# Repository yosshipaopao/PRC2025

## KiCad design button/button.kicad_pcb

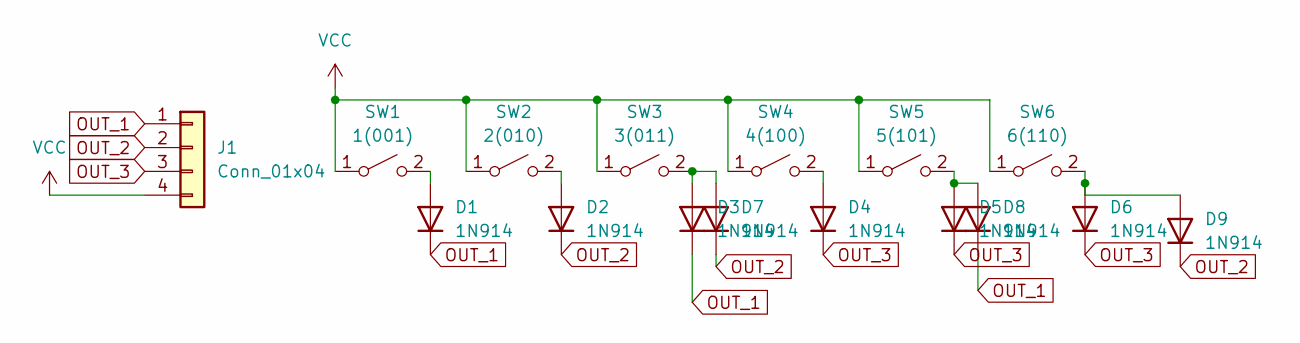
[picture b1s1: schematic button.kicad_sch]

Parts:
D1, D2, D3, D4, D5, D6, D7, D8, D9: 1N914; D_SOD-523
J1: Conn_01x04; PinSocket_1x04_P2.54mm_Vertical
SW1: 1(001); SW_PUSH_6mm
SW2: 2(010); SW_PUSH_6mm
SW3: 3(011); SW_PUSH_6mm
SW4: 4(100); SW_PUSH_6mm
SW5: 5(101); SW_PUSH_6mm
SW6: 6(110); SW_PUSH_6mm

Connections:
unnamed: D1.2 (A), SW1.2 (B)
unnamed: D2.2 (A), SW2.2 (B)
unnamed: D3.2 (A), D7.2 (A), SW3.2 (B)
unnamed: D4.2 (A), SW4.2 (B)
unnamed: D5.2 (A), D8.2 (A), SW5.2 (B)
unnamed: D6.2 (A), D9.2 (A), SW6.2 (B)
OUT_1: D1.1 (K), D3.1 (K), D8.1 (K), J1.1
OUT_2: D2.1 (K), D7.1 (K), D9.1 (K), J1.2
OUT_3: D4.1 (K), D5.1 (K), D6.1 (K), J1.3
VCC: J1.4, SW1.1 (A), SW2.1 (A), SW3.1 (A), SW4.1 (A), SW5.1 (A), SW6.1 (A)

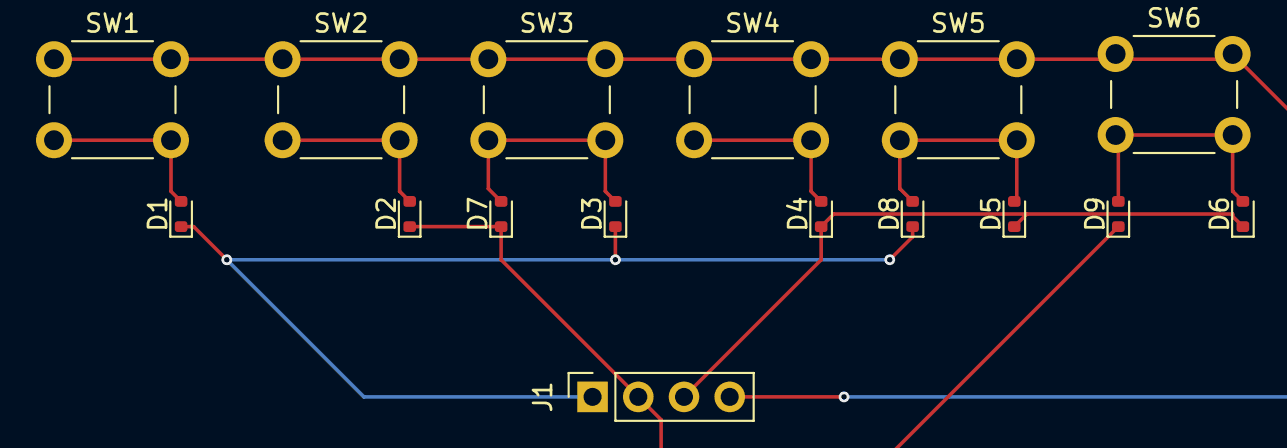
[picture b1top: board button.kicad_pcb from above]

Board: 2 copper layers, 16 parts (0 on the bottom side), 10 nets.

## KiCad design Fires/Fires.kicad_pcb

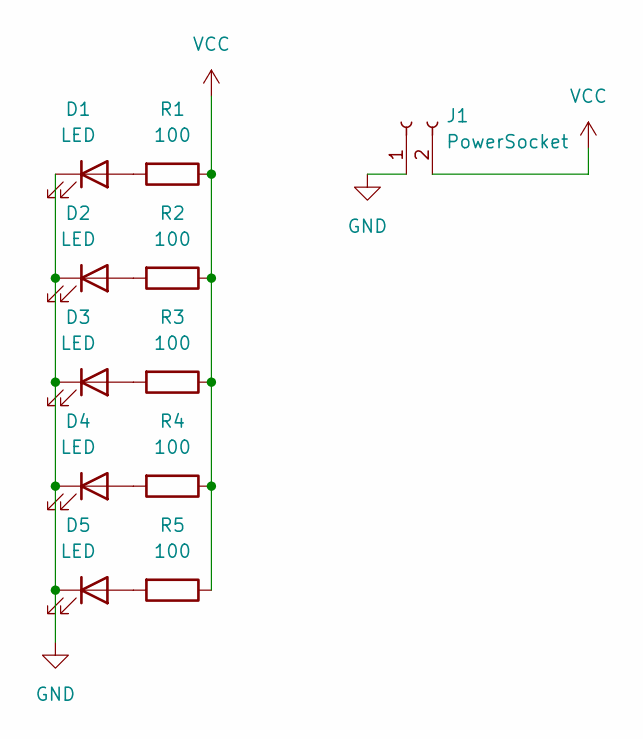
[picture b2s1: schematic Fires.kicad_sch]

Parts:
D1, D2, D3, D4, D5: LED; LED_D3.0mm
J1: PowerSocket; PinSocket_1x02_P2.54mm_Vertical
R1, R2, R3, R4, R5: 100; R_0603_1608Metric

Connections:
GND: D1.1 (K), D2.1 (K), D3.1 (K), D4.1 (K), D5.1 (K), J1.1
unnamed: D1.2 (A), R1.2
unnamed: D2.2 (A), R2.2
unnamed: D3.2 (A), R3.2
unnamed: D4.2 (A), R4.2
unnamed: D5.2 (A), R5.2
VCC: J1.2, R1.1, R2.1, R3.1, R4.1, R5.1

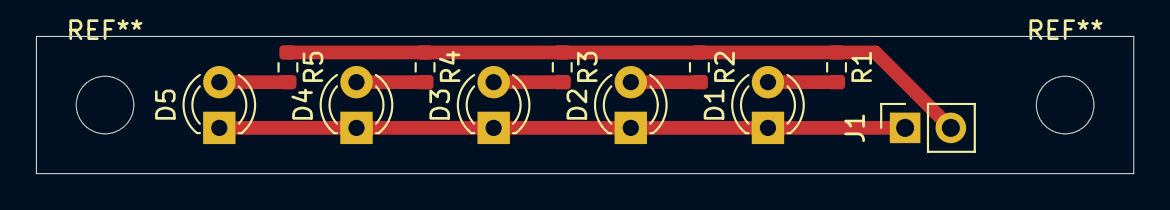
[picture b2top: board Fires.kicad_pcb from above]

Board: 2 copper layers, 61.0 x 7.6 mm, 11 parts (0 on the bottom side), 7 nets.

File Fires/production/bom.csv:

Designator,Footprint,Quantity,Value,LCSC Part #
"D1, D2, D3, D4, D5",LED_D3.0mm,5,LED,
J1,PinSocket_1x02_P2.54mm_Vertical,1,PowerSocket,
"R1, R2, R3, R4, R5",0603,5,100,

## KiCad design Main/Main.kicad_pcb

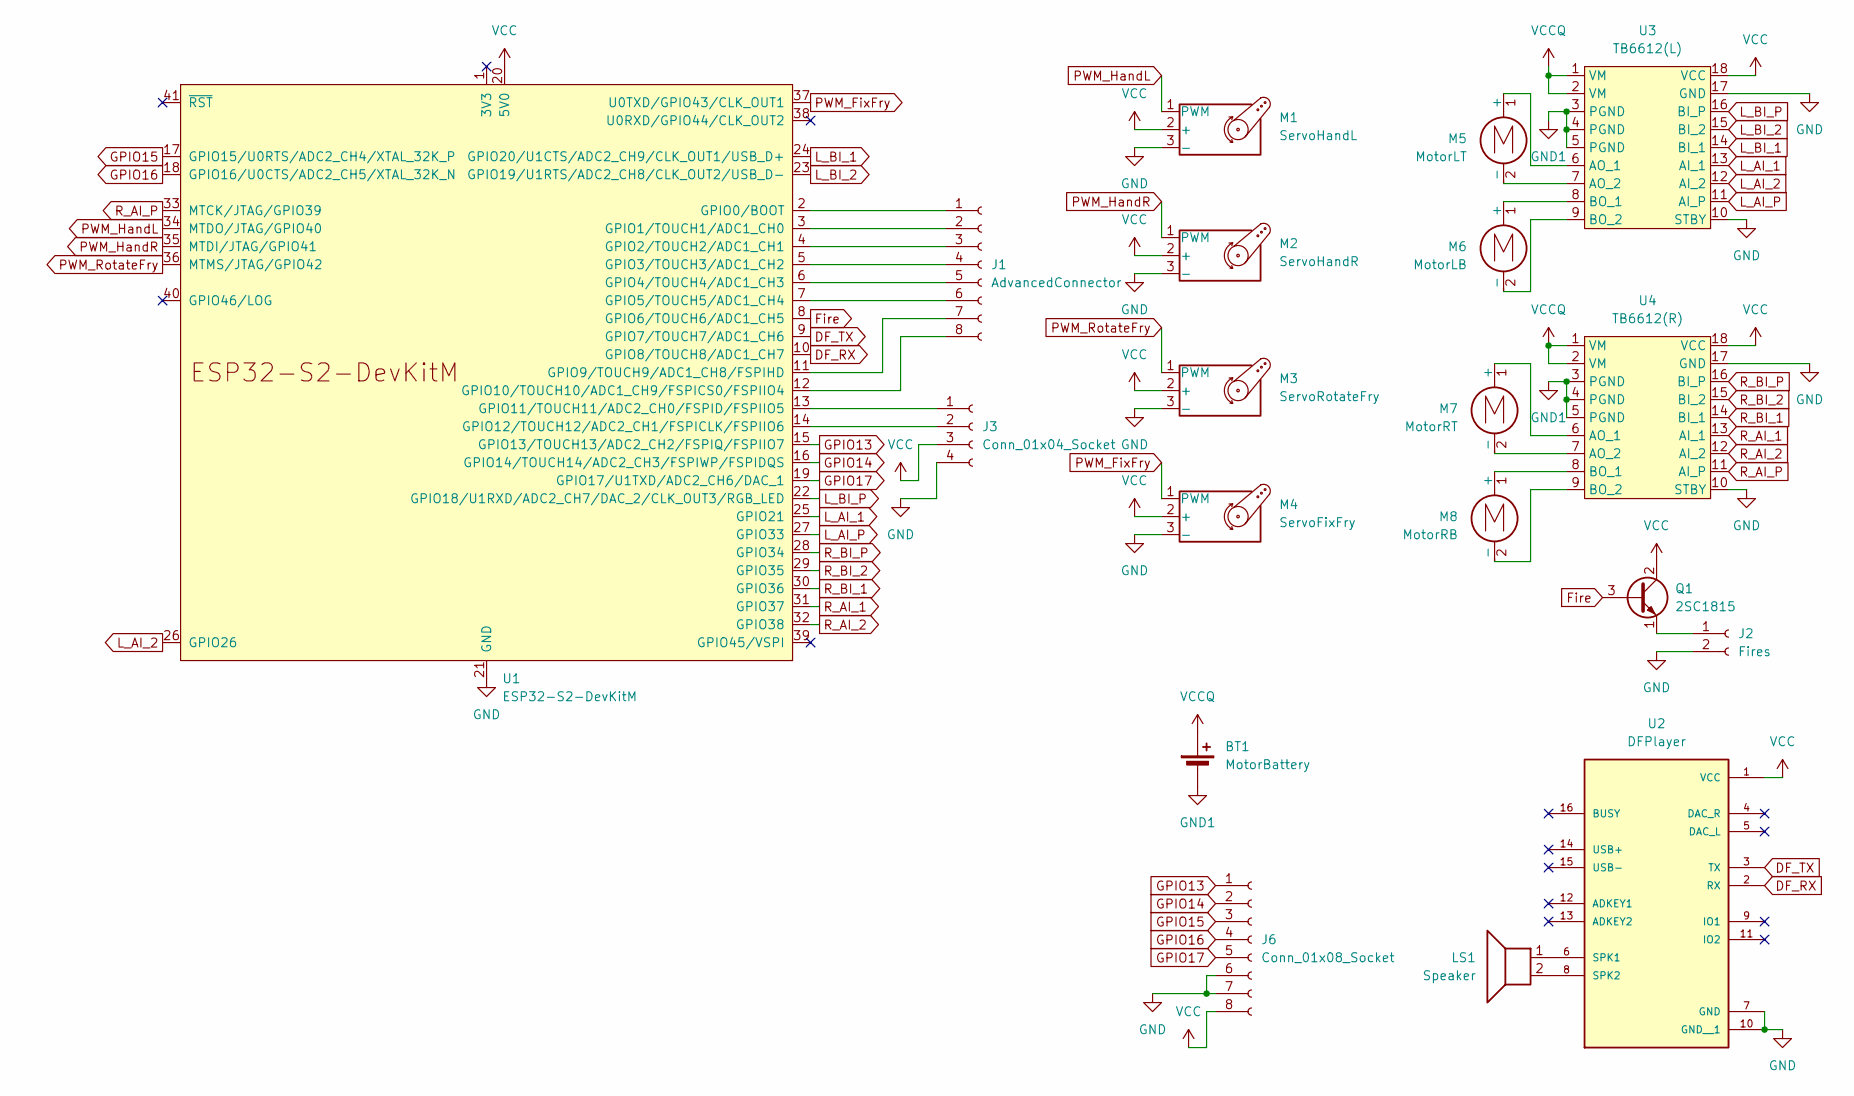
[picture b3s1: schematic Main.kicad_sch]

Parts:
BT1: MotorBattery; PinSocket_1x02_P2.54mm_Vertical
J1: AdvancedConnector; PinSocket_1x08_P2.54mm_Vertical
J2: Fires; PinSocket_1x02_P2.54mm_Vertical
J3: Conn_01x04_Socket; PinSocket_1x04_P2.54mm_Vertical
J6: Conn_01x08_Socket; PinSocket_1x08_P2.54mm_Vertical
LS1: Speaker; PinSocket_1x02_P2.54mm_Vertical
M1: ServoHandL; PinHeader_1x03_P2.54mm_Vertical
M2: ServoHandR; PinHeader_1x03_P2.54mm_Vertical
M3: ServoRotateFry; PinHeader_1x03_P2.54mm_Vertical
M4: ServoFixFry; PinHeader_1x03_P2.54mm_Vertical
M5: MotorLT; PinSocket_1x02_P2.54mm_Vertical
M6: MotorLB; PinSocket_1x02_P2.54mm_Vertical
M7: MotorRT; PinSocket_1x02_P2.54mm_Vertical
M8: MotorRB; PinSocket_1x02_P2.54mm_Vertical
Q1: 2SC1815; TO-92_Inline
U1: ESP32-S2-DevKitM
U2: DFPlayer; MODULE_DFR0299
U3: TB6612(L); TB6612
U4: TB6612(R); TB6612

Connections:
DF_RX: U1.10 (GPIO8/TOUCH8/ADC1_CH7), U2.2 (RX)
DF_TX: U1.9 (GPIO7/TOUCH7/ADC1_CH6), U2.3 (TX)
Fire: Q1.3 (B), U1.8 (GPIO6/TOUCH6/ADC1_CH5)
GND: J2.2, J3.4, J6.6, J6.7, M1.3 (-), M2.3 (-), M3.3 (-), M4.3 (-), U1.21 (GND), U1.42 (GND), U2.7 (GND), U2.10 (GND__1), U3.10 (STBY), U3.17 (GND), U4.10 (STBY), U4.17 (GND)
GND1: BT1.2 (-), U3.3 (PGND), U3.4 (PGND), U3.5 (PGND), U4.3 (PGND), U4.4 (PGND), U4.5 (PGND)
GPIO13: J6.1, U1.15 (GPIO13/TOUCH13/ADC2_CH2/FSPIQ/FSPIIO7)
GPIO14: J6.2, U1.16 (GPIO14/TOUCH14/ADC2_CH3/FSPIWP/FSPIDQS)
GPIO15: J6.3, U1.17 (GPIO15/U0RTS/ADC2_CH4/XTAL_32K_P)
GPIO16: J6.4, U1.18 (GPIO16/U0CTS/ADC2_CH5/XTAL_32K_N)
GPIO17: J6.5, U1.19 (GPIO17/U1TXD/ADC2_CH6/DAC_1)
L_AI_1: U1.25 (GPIO21), U3.13 (AI_1)
L_AI_2: U1.26 (GPIO26), U3.12 (AI_2)
L_AI_P: U1.27 (GPIO33), U3.11 (AI_P)
L_BI_1: U1.24 (GPIO20/U1CTS/ADC2_CH9/CLK_OUT1/USB_D+), U3.14 (BI_1)
L_BI_2: U1.23 (GPIO19/U1RTS/ADC2_CH8/CLK_OUT2/USB_D-), U3.15 (BI_2)
L_BI_P: U1.22 (GPIO18/U1RXD/ADC2_CH7/DAC_2/CLK_OUT3/RG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), U3.16 (BI_P)
unnamed: J1.1, U1.2 (GPIO0/BOOT)
unnamed: J1.2, U1.3 (GPIO1/TOUCH1/ADC1_CH0)
unnamed: J1.3, U1.4 (GPIO2/TOUCH2/ADC1_CH1)
unnamed: J1.4, U1.5 (GPIO3/TOUCH3/ADC1_CH2)
unnamed: J1.5, U1.6 (GPIO4/TOUCH4/ADC1_CH3)
unnamed: J1.6, U1.7 (GPIO5/TOUCH5/ADC1_CH4)
unnamed: J1.7, U1.11 (GPIO9/TOUCH9/ADC1_CH8/FSPIHD)
unnamed: J1.8, U1.12 (GPIO10/TOUCH10/ADC1_CH9/FSPICS0/FSPIIO4)
unnamed: J2.1, Q1.1 (E)
unnamed: J3.1, U1.13 (GPIO11/TOUCH11/ADC2_CH0/FSPID/FSPIIO5)
unnamed: J3.2, U1.14 (GPIO12/TOUCH12/ADC2_CH1/FSPICLK/FSPIIO6)
unnamed: M5.1 (+), U3.6 (AO_1)
unnamed: M5.2 (-), U3.7 (AO_2)
unnamed: M6.1 (+), U3.8 (BO_1)
unnamed: M6.2 (-), U3.9 (BO_2)
unnamed: M7.1 (+), U4.6 (AO_1)
unnamed: M7.2 (-), U4.7 (AO_2)
unnamed: M8.1 (+), U4.8 (BO_1)
unnamed: M8.2 (-), U4.9 (BO_2)
unnamed: LS1.1, U2.6 (SPK1)
unnamed: LS1.2, U2.8 (SPK2)
PWM_FixFry: M4.1 (PWM), U1.37 (U0TXD/GPIO43/CLK_OUT1)
PWM_HandL: M1.1 (PWM), U1.34 (MTDO/JTAG/GPIO40)
PWM_HandR: M2.1 (PWM), U1.35 (MTDI/JTAG/GPIO41)
PWM_RotateFry: M3.1 (PWM), U1.36 (MTMS/JTAG/GPIO42)
R_AI_1: U1.31 (GPIO37), U4.13 (AI_1)
R_AI_2: U1.32 (GPIO38), U4.12 (AI_2)
R_AI_P: U1.33 (MTCK/JTAG/GPIO39), U4.11 (AI_P)
R_BI_1: U1.30 (GPIO36), U4.14 (BI_1)
R_BI_2: U1.29 (GPIO35), U4.15 (BI_2)
R_BI_P: U1.28 (GPIO34), U4.16 (BI_P)
VCC: J3.3, J6.8, M1.2 (+), M2.2 (+), M3.2 (+), M4.2 (+), Q1.2 (C), U1.20 (5V0), U2.1 (VCC), U3.18 (VCC), U4.18 (VCC)
VCCQ: BT1.1 (+), U3.1 (VM), U3.2 (VM), U4.1 (VM), U4.2 (VM)

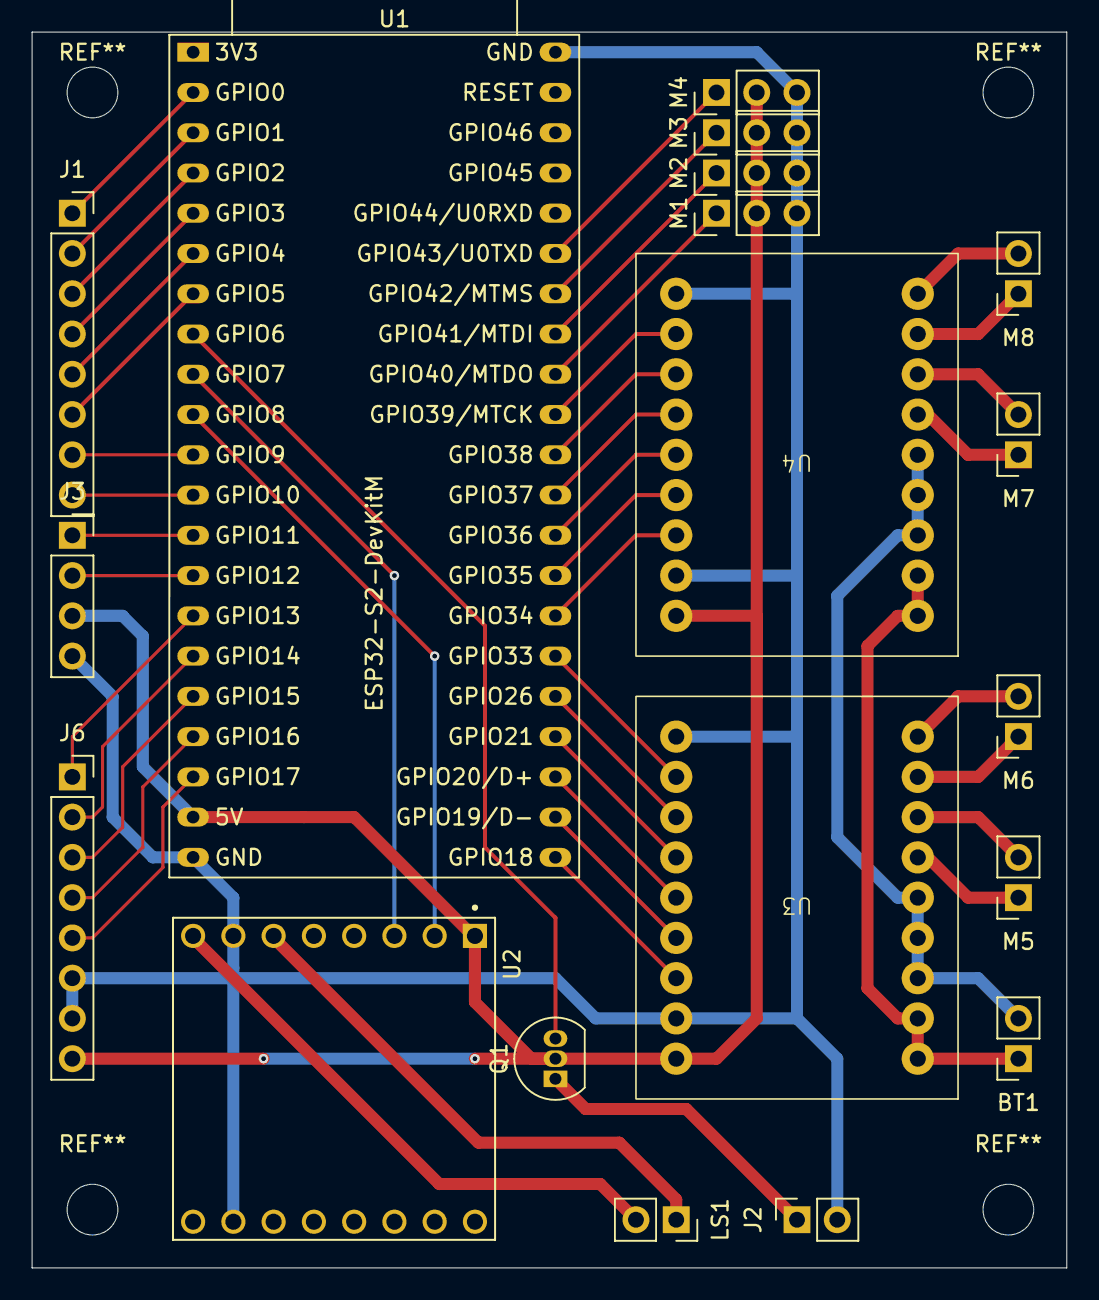
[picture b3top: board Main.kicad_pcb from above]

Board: 2 copper layers, 65.3 x 78.0 mm, 19 parts (0 on the bottom side), 49 nets.

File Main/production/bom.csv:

Designator,Footprint,Quantity,Value,LCSC Part #
BT1,PinSocket_1x02_P2.54mm_Vertical,1,MotorBattery,
J1,PinSocket_1x08_P2.54mm_Vertical,1,AdvancedConnector,
J2,PinSocket_1x02_P2.54mm_Vertical,1,Fires,
J3,PinSocket_1x04_P2.54mm_Vertical,1,Conn_01x04_Socket,
J6,PinSocket_1x08_P2.54mm_Vertical,1,Conn_01x08_Socket,
LS1,PinSocket_1x02_P2.54mm_Vertical,1,Speaker,
M1,PinHeader_1x03_P2.54mm_Vertical,1,ServoHandL,
M2,PinHeader_1x03_P2.54mm_Vertical,1,ServoHandR,
M3,PinHeader_1x03_P2.54mm_Vertical,1,ServoRotateFry,
M4,PinHeader_1x03_P2.54mm_Vertical,1,ServoFixFry,
M5,PinSocket_1x02_P2.54mm_Vertical,1,MotorLT,
M6,PinSocket_1x02_P2.54mm_Vertical,1,MotorLB,
M7,PinSocket_1x02_P2.54mm_Vertical,1,MotorRT,
M8,PinSocket_1x02_P2.54mm_Vertical,1,MotorRB,
Q1,TO-92_Inline,1,2SC1815,
U1,ESP32-S2-DevKitM,1,ESP32-S2-DevKitM,
U2,MODULE_DFR0299,1,DFPlayer,
U3,TB6612,1,TB6612(L),
U4,TB6612,1,TB6612(R),

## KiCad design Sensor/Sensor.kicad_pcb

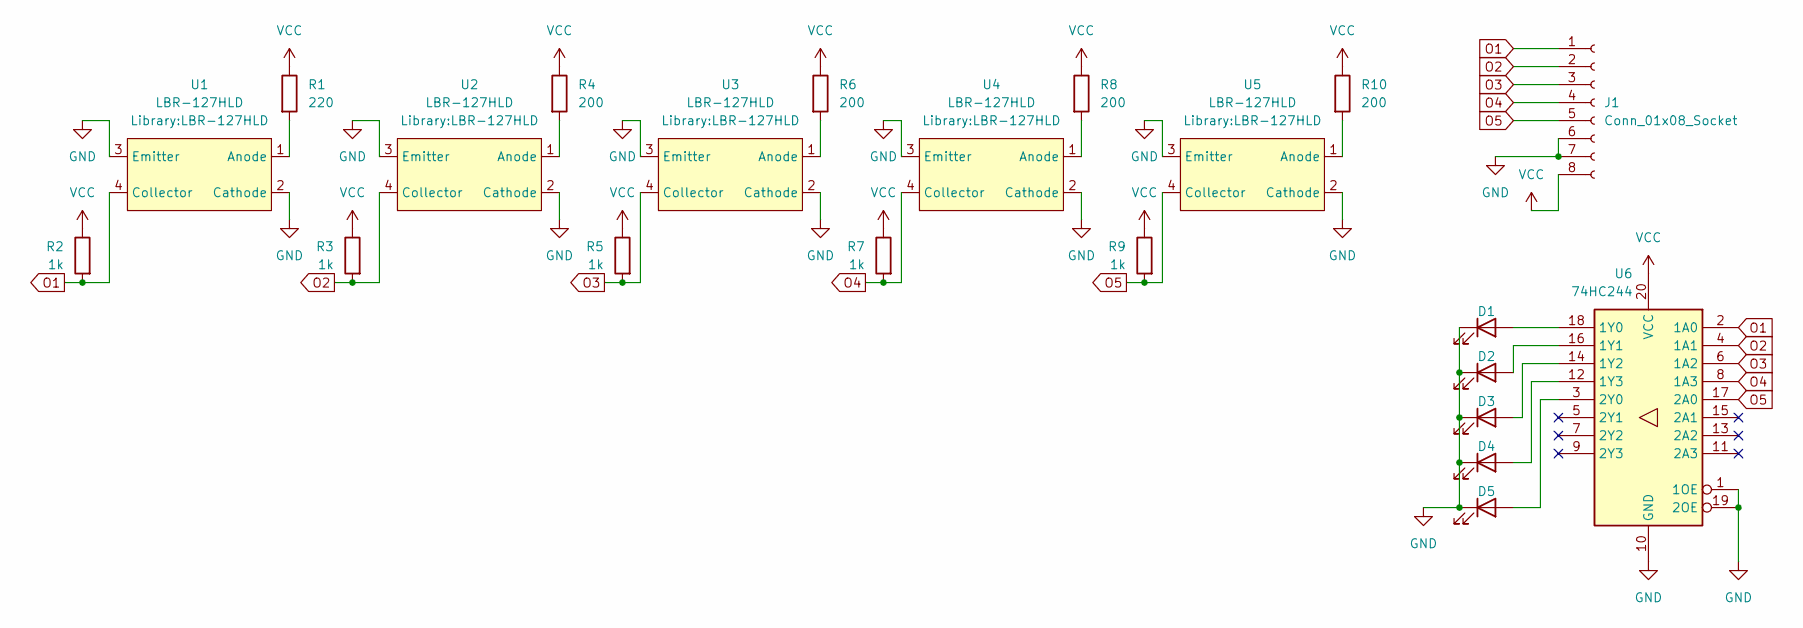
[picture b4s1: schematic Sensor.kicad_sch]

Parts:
D1, D2, D3, D4, D5: LED; LED_0603_1608Metric
J1: Conn_01x08_Socket; PinSocket_1x08_P2.54mm_Vertical
R1: 220; R_0603_1608Metric
R2, R3, R5, R7, R9: 1k; R_0603_1608Metric
R4, R6, R8, R10: 200; R_0603_1608Metric
U1, U2, U3, U4, U5: LBR-127HLD
U6: 74HC244; SSOP-20_4.4x6.5mm_P0.65mm

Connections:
GND: D1.1 (K), D2.1 (K), D3.1 (K), D4.1 (K), D5.1 (K), J1.6, J1.7, U1.2 (Cathode), U1.3 (Emitter), U2.2 (Cathode), U2.3 (Emitter), U3.2 (Cathode), U3.3 (Emitter), U4.2 (Cathode), U4.3 (Emitter), U5.2 (Cathode), U5.3 (Emitter), U6.1 (1OE), U6.10 (GND), U6.19 (2OE)
unnamed: D1.2 (A), U6.18 (1Y0)
unnamed: D2.2 (A), U6.16 (1Y1)
unnamed: D3.2 (A), U6.14 (1Y2)
unnamed: D4.2 (A), U6.12 (1Y3)
unnamed: D5.2 (A), U6.3 (2Y0)
unnamed: R1.2, U1.1 (Anode)
unnamed: R4.2, U2.1 (Anode)
unnamed: R6.2, U3.1 (Anode)
unnamed: R8.2, U4.1 (Anode)
unnamed: R10.2, U5.1 (Anode)
O1: J1.1, R2.2, U1.4 (Collector), U6.2 (1A0)
O2: J1.2, R3.2, U2.4 (Collector), U6.4 (1A1)
O3: J1.3, R5.2, U3.4 (Collector), U6.6 (1A2)
O4: J1.4, R7.2, U4.4 (Collector), U6.8 (1A3)
O5: J1.5, R9.2, U5.4 (Collector), U6.17 (2A0)
VCC: J1.8, R1.1, R2.1, R3.1, R4.1, R5.1, R6.1, R7.1, R8.1, R9.1, R10.1, U6.20 (VCC)

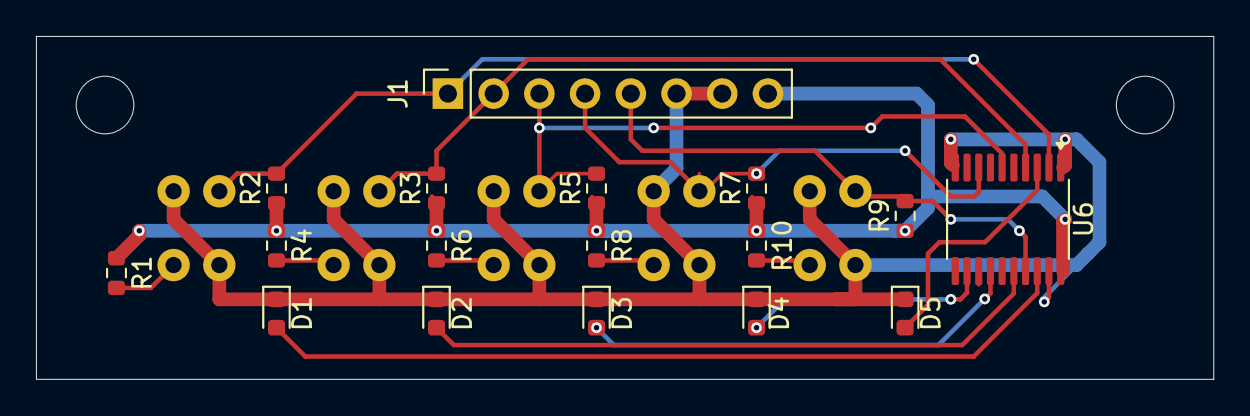
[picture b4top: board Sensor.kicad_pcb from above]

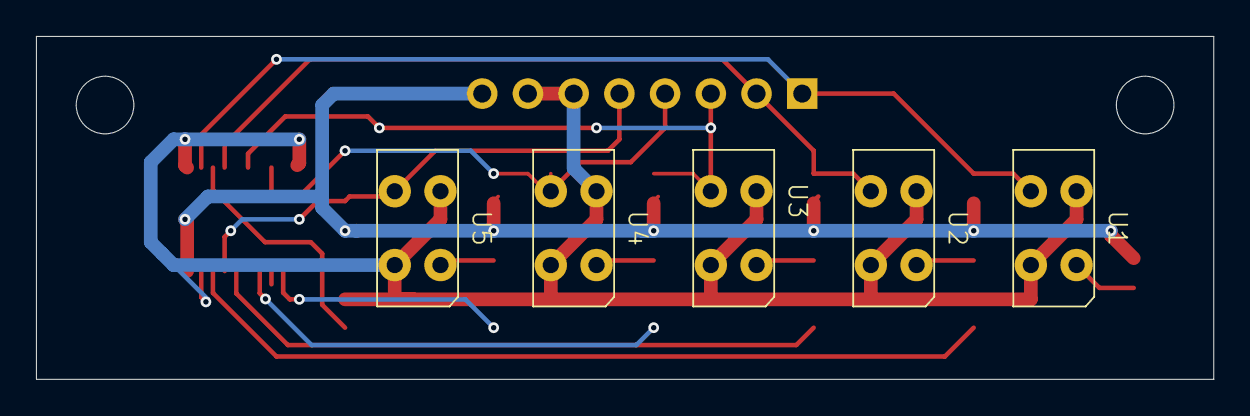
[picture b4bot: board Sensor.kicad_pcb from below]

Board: 2 copper layers, 65.4 x 19.0 mm, 22 parts (5 on the bottom side), 17 nets.

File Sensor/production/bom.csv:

Designator,Footprint,Quantity,Value,LCSC Part #
"D1, D2, D3, D4, D5",0603,5,LED,
J1,PinSocket_1x08_P2.54mm_Vertical,1,Conn_01x08_Socket,
R1,0603,1,220,
"R10, R4, R6, R8",0603,4,200,
"R2, R3, R5, R7, R9",0603,5,1k,
"U1, U2, U3, U4, U5",LBR-127HLD,5,LBR-127HLD,
U6,SSOP-20_4.4x6.5mm_P0.65mm,1,74HC244,

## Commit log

2025-11-19 add fires and sensor
2025-11-20 main cir
2025-11-22 up main
2025-12-10 センサー関係忘れてた
2025-12-10 kicadで開きながらコミットしちゃダメって言ったでしょ！
2025-12-10 出力を追加
